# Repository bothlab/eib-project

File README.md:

# ST4 Intan Amplifier Boards & EIBs

Electrode Interface Boards and Amplifier Boards for use with the Intan RHD DAQ system

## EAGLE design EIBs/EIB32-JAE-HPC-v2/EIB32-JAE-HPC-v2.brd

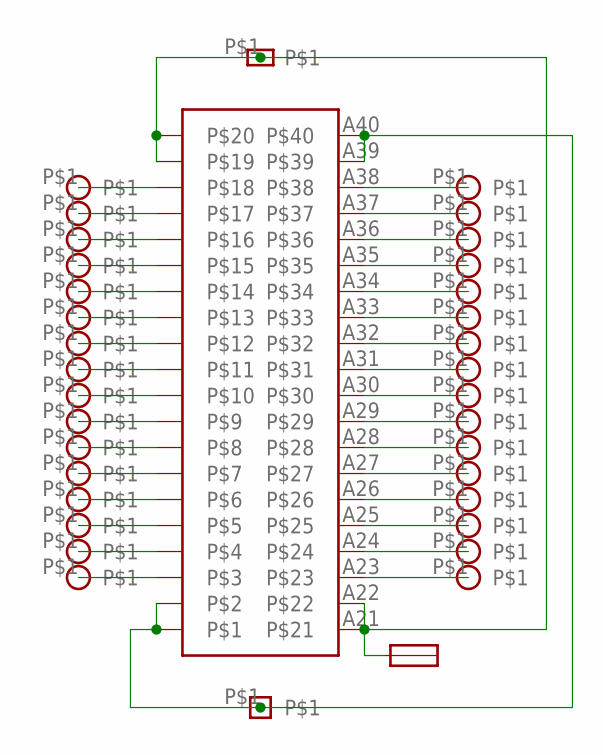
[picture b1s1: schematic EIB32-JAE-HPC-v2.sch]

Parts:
U$1: WR-40SB-VFH30
U$2: EIB-GND-HOLE-PAD-SMALL
U$3: EIB-GND-HOLE-PAD
U$4: JMP-PAD-SMALL
U$5, U$6, U$7, U$8, U$9, U$10, U$11, U$12, U$13, U$14, U$15, U$16, U$17, U$18, U$19, U$20, U$23, U$24, U$25, U$26, U$27, U$28, U$29, U$30, U$31, U$32, U$33, U$34, U$35, U$36, U$37, U$38: EIB-TETRODE-HOLE-RS-PAD

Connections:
unnamed: U$1.A19, U$1.A20, U$1.A21, U$1.A22, U$2.P$1, U$4.P$1
unnamed: U$1.A1, U$1.A2, U$1.A39, U$1.A40, U$3.P$1
unnamed: U$1.A18, U$5.P$1
unnamed: U$1.A17, U$6.P$1
unnamed: U$1.A16, U$7.P$1
unnamed: U$1.A15, U$8.P$1
unnamed: U$1.A14, U$9.P$1
unnamed: U$1.A13, U$10.P$1
unnamed: U$1.A12, U$11.P$1
unnamed: U$1.A11, U$12.P$1
unnamed: U$1.A10, U$13.P$1
unnamed: U$1.A9, U$14.P$1
unnamed: U$1.A8, U$15.P$1
unnamed: U$1.A7, U$16.P$1
unnamed: U$1.A6, U$17.P$1
unnamed: U$1.A5, U$18.P$1
unnamed: U$1.A4, U$19.P$1
unnamed: U$1.A3, U$20.P$1
unnamed: U$1.A38, U$23.P$1
unnamed: U$1.A37, U$24.P$1
unnamed: U$1.A36, U$25.P$1
unnamed: U$1.A35, U$26.P$1
unnamed: U$1.A34, U$27.P$1
unnamed: U$1.A33, U$28.P$1
unnamed: U$1.A32, U$29.P$1
unnamed: U$1.A31, U$30.P$1
unnamed: U$1.A30, U$31.P$1
unnamed: U$1.A29, U$32.P$1
unnamed: U$1.A28, U$33.P$1
unnamed: U$1.A27, U$34.P$1
unnamed: U$1.A26, U$35.P$1
unnamed: U$1.A25, U$36.P$1
unnamed: U$1.A24, U$37.P$1
unnamed: U$1.A23, U$38.P$1

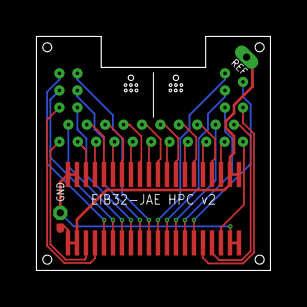
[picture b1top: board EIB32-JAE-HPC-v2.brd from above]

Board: 2 copper layers, 13.0 x 13.0 mm, 36 parts (0 on the bottom side), 34 nets.

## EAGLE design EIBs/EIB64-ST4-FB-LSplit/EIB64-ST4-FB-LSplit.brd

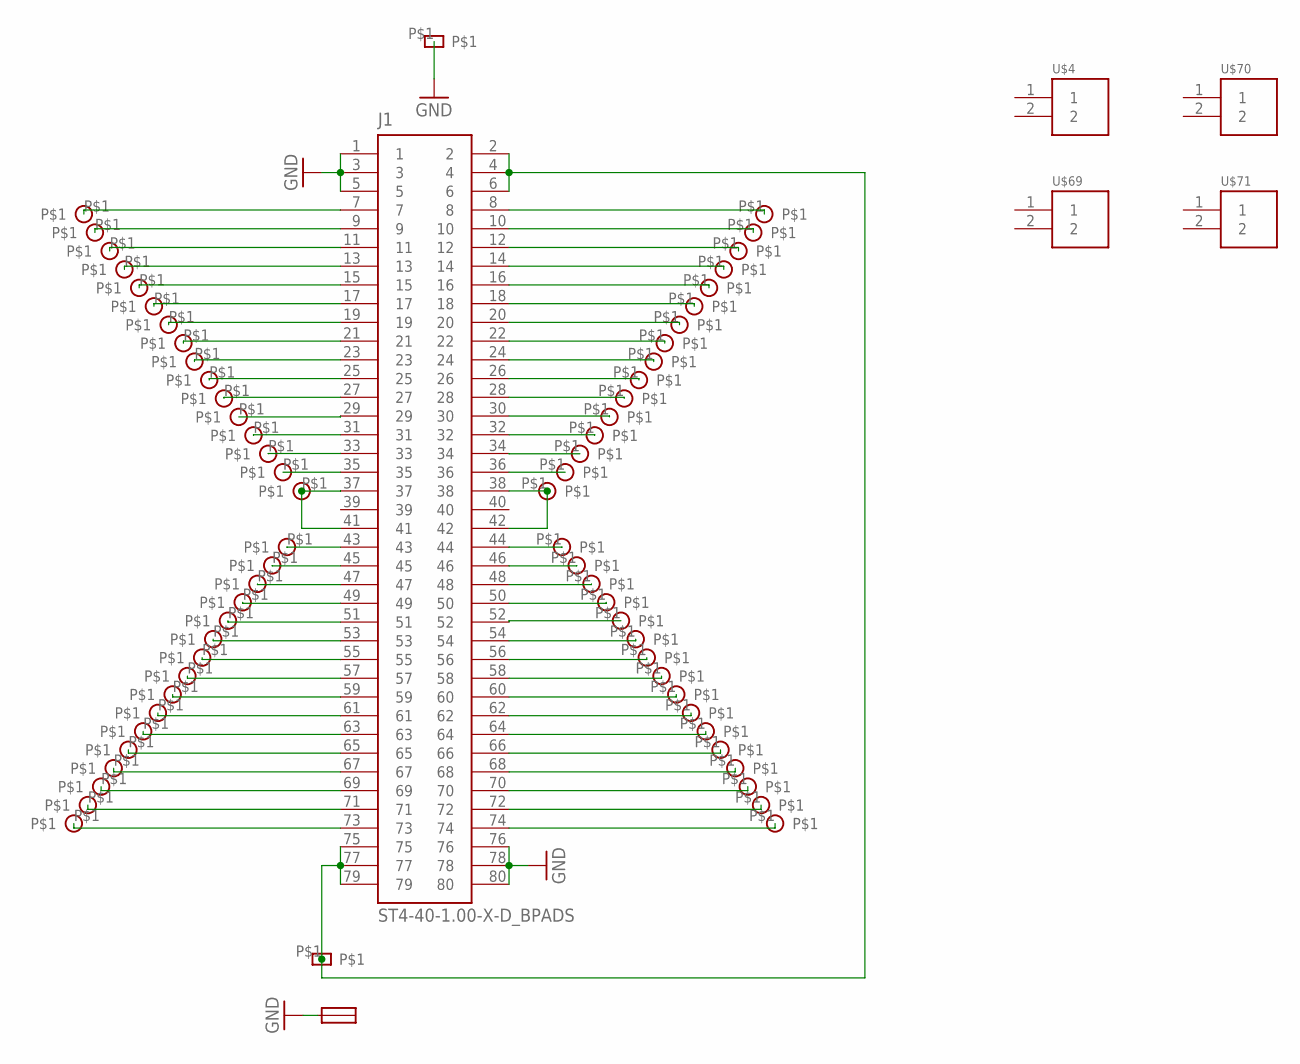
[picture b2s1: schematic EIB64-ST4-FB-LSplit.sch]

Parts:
J1: ST4-40-1.00-X-D_BPADS
U$1, U$3: EIB-GND-HOLE-PAD-SMALL
U$2: JMP-PAD-SMALL
U$4, U$69, U$70, U$71: THCONLY_TMS-102-XX-XX-S
U$5, U$6, U$7, U$8, U$9, U$10, U$11, U$12, U$13, U$14, U$15, U$16, U$17, U$18, U$19, U$20, U$21, U$22, U$23, U$24, U$25, U$26, U$27, U$28, U$29, U$30, U$31, U$32, U$33, U$34, U$35, U$36, U$37, U$38, U$39, U$40, U$41, U$42, U$43, U$44, U$45, U$46, U$47, U$48, U$49, U$50, U$51, U$52, U$53, U$54, U$55, U$56, U$57, U$58, U$59, U$60, U$61, U$62, U$63, U$64, U$65, U$66, U$67, U$68: EIB-TETRODE-HOLE-RS-PAD

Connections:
GND: J1.1, J1.3, J1.5, J1.76, J1.78, J1.80, U$1.P$1, U$2.P$1
unnamed: J1.2, J1.4, J1.6, J1.75, J1.77, J1.79, U$3.P$1
unnamed: J1.35, U$7.P$1
unnamed: J1.36, U$5.P$1
unnamed: J1.34, U$9.P$1
unnamed: J1.20, U$16.P$1
unnamed: J1.22, U$15.P$1
unnamed: J1.24, U$14.P$1
unnamed: J1.26, U$13.P$1
unnamed: J1.28, U$12.P$1
unnamed: J1.30, U$11.P$1
unnamed: J1.37, J1.41, U$8.P$1
unnamed: J1.32, U$10.P$1
unnamed: J1.74, U$52.P$1
unnamed: J1.18, U$17.P$1
unnamed: J1.16, U$18.P$1
unnamed: J1.14, U$19.P$1
unnamed: J1.12, U$20.P$1
unnamed: J1.10, U$21.P$1
unnamed: J1.8, U$22.P$1
unnamed: J1.33, U$23.P$1
unnamed: J1.31, U$24.P$1
unnamed: J1.29, U$25.P$1
unnamed: J1.27, U$26.P$1
unnamed: J1.25, U$27.P$1
unnamed: J1.23, U$28.P$1
unnamed: J1.21, U$29.P$1
unnamed: J1.19, U$30.P$1
unnamed: J1.17, U$31.P$1
unnamed: J1.15, U$32.P$1
unnamed: J1.13, U$33.P$1
unnamed: J1.11, U$34.P$1
unnamed: J1.9, U$35.P$1
unnamed: J1.7, U$36.P$1
unnamed: J1.72, U$51.P$1
unnamed: J1.70, U$50.P$1
unnamed: J1.68, U$49.P$1
unnamed: J1.66, U$48.P$1
unnamed: J1.64, U$47.P$1
unnamed: J1.62, U$46.P$1
unnamed: J1.60, U$45.P$1
unnamed: J1.58, U$44.P$1
unnamed: J1.56, U$43.P$1
unnamed: J1.54, U$42.P$1
unnamed: J1.52, U$41.P$1
unnamed: J1.50, U$40.P$1
unnamed: J1.48, U$39.P$1
unnamed: J1.46, U$38.P$1
unnamed: J1.44, U$37.P$1
unnamed: J1.38, J1.42, U$6.P$1
unnamed: J1.43, U$53.P$1
unnamed: J1.45, U$54.P$1
unnamed: J1.47, U$55.P$1
unnamed: J1.49, U$56.P$1
unnamed: J1.51, U$57.P$1
unnamed: J1.53, U$58.P$1
unnamed: J1.55, U$59.P$1
unnamed: J1.57, U$60.P$1
unnamed: J1.59, U$61.P$1
unnamed: J1.61, U$62.P$1
unnamed: J1.63, U$63.P$1
unnamed: J1.65, U$64.P$1
unnamed: J1.67, U$65.P$1
unnamed: J1.69, U$66.P$1
unnamed: J1.71, U$67.P$1
unnamed: J1.73, U$68.P$1

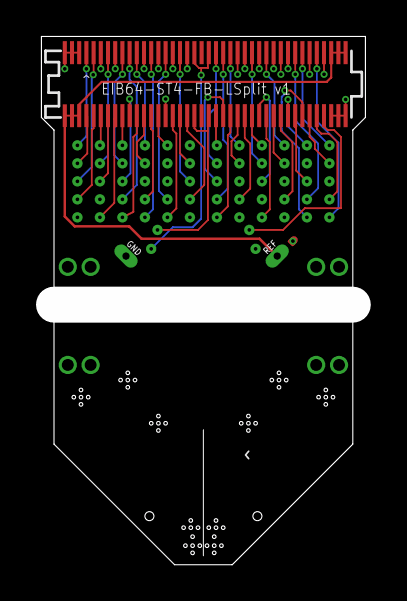
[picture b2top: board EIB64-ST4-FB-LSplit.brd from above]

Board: 4 copper layers, 18.0 x 29.4 mm, 72 parts (0 on the bottom side), 66 nets.

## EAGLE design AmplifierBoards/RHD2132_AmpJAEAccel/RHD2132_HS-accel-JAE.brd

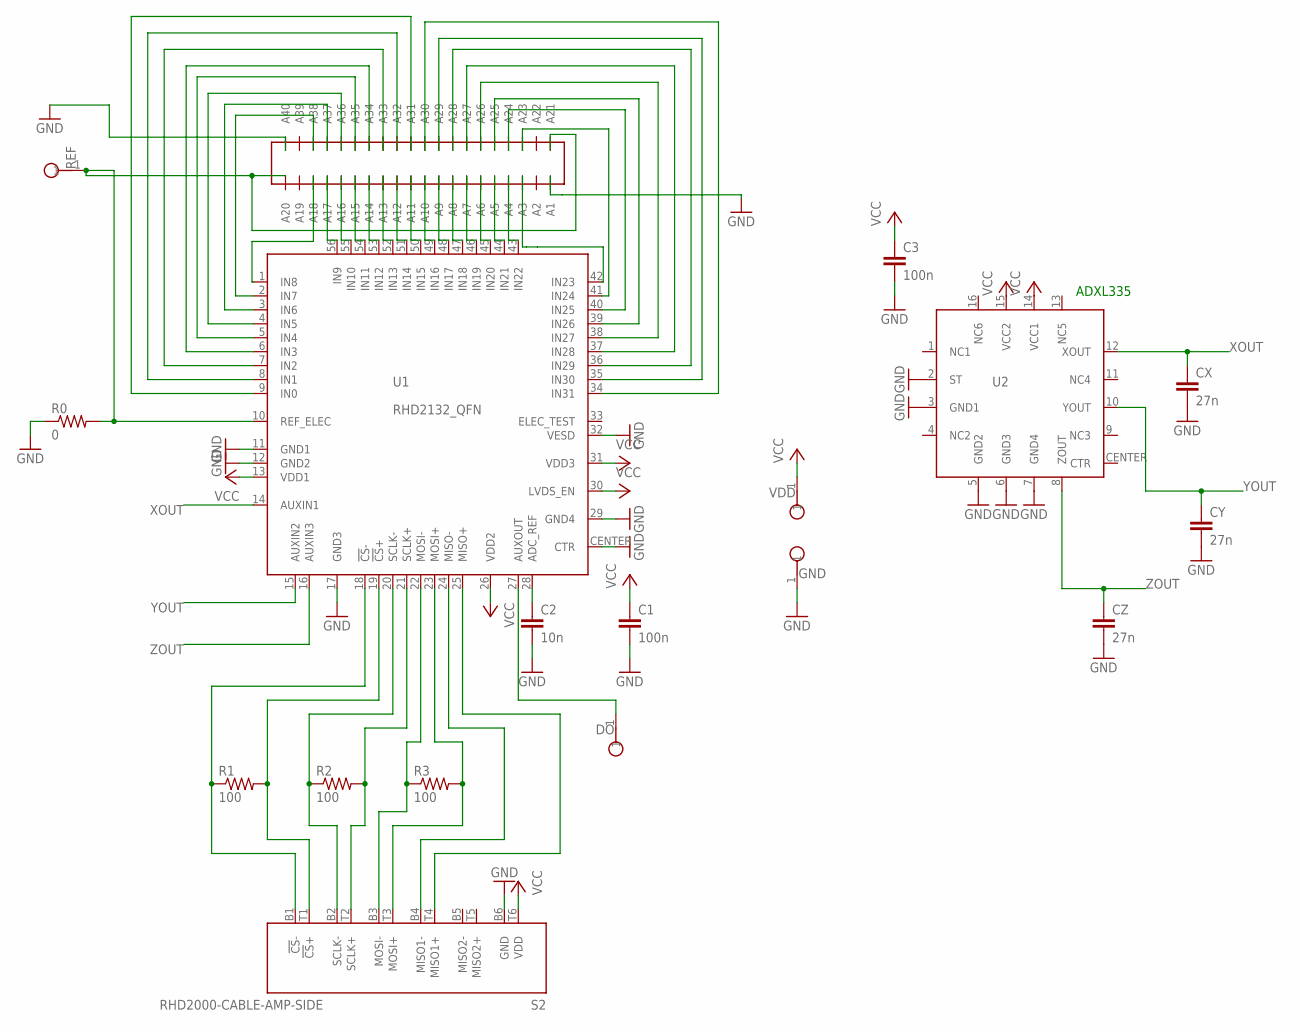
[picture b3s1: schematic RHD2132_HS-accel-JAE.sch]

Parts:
C1, C3: 100n; 0402
C2: 10n; 0402
CX: 27n; 0402
CY: 27n; 0402
CZ: 27n; 0402
DO: TESTPOINT_SMALL
GND: TESTPOINT_SMALL
R0: 0; 0402
R1, R2, R3: 100; 0402
REF: TESTPOINT_SMALL
S2: RHD2000-CABLE-AMP-SIDE; OMNETICS_PZN-12-AA
U1: RHD2132_QFN; QFN56_8_X_8_LARGE
U2: ADXL335
U$1: WR-40P-HFHD
VDD: TESTPOINT_SMALL

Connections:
GND: C1.2, C2.2, C3.2, CX.2, CY.2, CZ.2, GND.1, R0.1, S2.B6 (GND), U1.11 (GND1), U1.12 (GND2), U1.17 (GND3), U1.29 (GND4), U1.32 (VESD), U1.CENTER (CTR), U2.2 (ST), U2.3 (GND1), U2.5 (GND2), U2.6 (GND3), U2.7 (GND4), U$1.P$1 (A1), U$1.P$40 (A40)
unnamed: U1.3 (IN6), U$1.P$37 (A37)
unnamed: U1.2 (IN7), U$1.P$38 (A38)
unnamed: U1.4 (IN5), U$1.P$36 (A36)
unnamed: U1.5 (IN4), U$1.P$35 (A35)
unnamed: U1.6 (IN3), U$1.P$34 (A34)
unnamed: U1.7 (IN2), U$1.P$33 (A33)
unnamed: U1.8 (IN1), U$1.P$32 (A32)
unnamed: U1.9 (IN0), U$1.P$31 (A31)
unnamed: U1.34 (IN31), U$1.P$30 (A30)
unnamed: R1.1, S2.B1 (!CS!-), U1.18 (!CS!-)
unnamed: U1.41 (IN24), U$1.P$23 (A23)
unnamed: U1.40 (IN25), U$1.P$24 (A24)
unnamed: U1.39 (IN26), U$1.P$25 (A25)
unnamed: U1.38 (IN27), U$1.P$26 (A26)
unnamed: U1.37 (IN28), U$1.P$27 (A27)
unnamed: U1.36 (IN29), U$1.P$28 (A28)
unnamed: U1.35 (IN30), U$1.P$29 (A29)
unnamed: U1.56 (IN9), U$1.P$17 (A17)
unnamed: U1.55 (IN10), U$1.P$16 (A16)
unnamed: U1.54 (IN11), U$1.P$15 (A15)
unnamed: U1.53 (IN12), U$1.P$14 (A14)
unnamed: U1.52 (IN13), U$1.P$13 (A13)
unnamed: U1.51 (IN14), U$1.P$12 (A12)
unnamed: U1.50 (IN15), U$1.P$11 (A11)
unnamed: U1.49 (IN16), U$1.P$10 (A10)
unnamed: U1.48 (IN17), U$1.P$9 (A9)
unnamed: U1.47 (IN18), U$1.P$8 (A8)
unnamed: U1.46 (IN19), U$1.P$7 (A7)
unnamed: U1.45 (IN20), U$1.P$6 (A6)
unnamed: U1.44 (IN21), U$1.P$5 (A5)
unnamed: U1.43 (IN22), U$1.P$4 (A4)
unnamed: U1.1 (IN8), U$1.P$18 (A18)
unnamed: U1.42 (IN23), U$1.P$3 (A3)
unnamed: R1.2, S2.T1 (!CS!+), U1.19 (!CS!+)
unnamed: R2.1, S2.B2 (SCLK-), U1.20 (SCLK-)
unnamed: R2.2, S2.T2 (SCLK+), U1.21 (SCLK+)
unnamed: R3.1, S2.B3 (MOSI-), U1.22 (MOSI-)
unnamed: R3.2, S2.T3 (MOSI+), U1.23 (MOSI+)
unnamed: S2.B4 (MISO1-), U1.24 (MISO-)
unnamed: S2.T4 (MISO1+), U1.25 (MISO+)
unnamed: C2.1, U1.28 (ADC_REF)
unnamed: DO.1, U1.27 (AUXOUT)
unnamed: R0.2, REF.1, U1.10 (REF_ELEC), U$1.P$20 (A20)
VCC: C1.1, C3.1, S2.T6 (VDD), U1.13 (VDD1), U1.26 (VDD2), U1.30 (LVDS_EN), U1.31 (VDD3), U2.14 (VCC1), U2.15 (VCC2), VDD.1
XOUT: CX.1, U1.14 (AUXIN1), U2.12 (XOUT)
YOUT: CY.1, U1.15 (AUXIN2), U2.10 (YOUT)
ZOUT: CZ.1, U1.16 (AUXIN3), U2.8 (ZOUT)

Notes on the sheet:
ADXL335

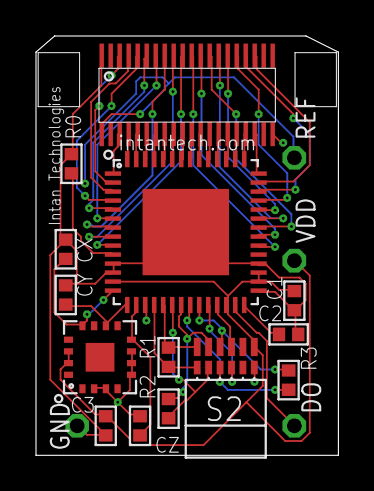
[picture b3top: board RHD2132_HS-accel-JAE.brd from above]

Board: 4 copper layers, 16.8 x 23.3 mm, 18 parts (0 on the bottom side), 48 nets.

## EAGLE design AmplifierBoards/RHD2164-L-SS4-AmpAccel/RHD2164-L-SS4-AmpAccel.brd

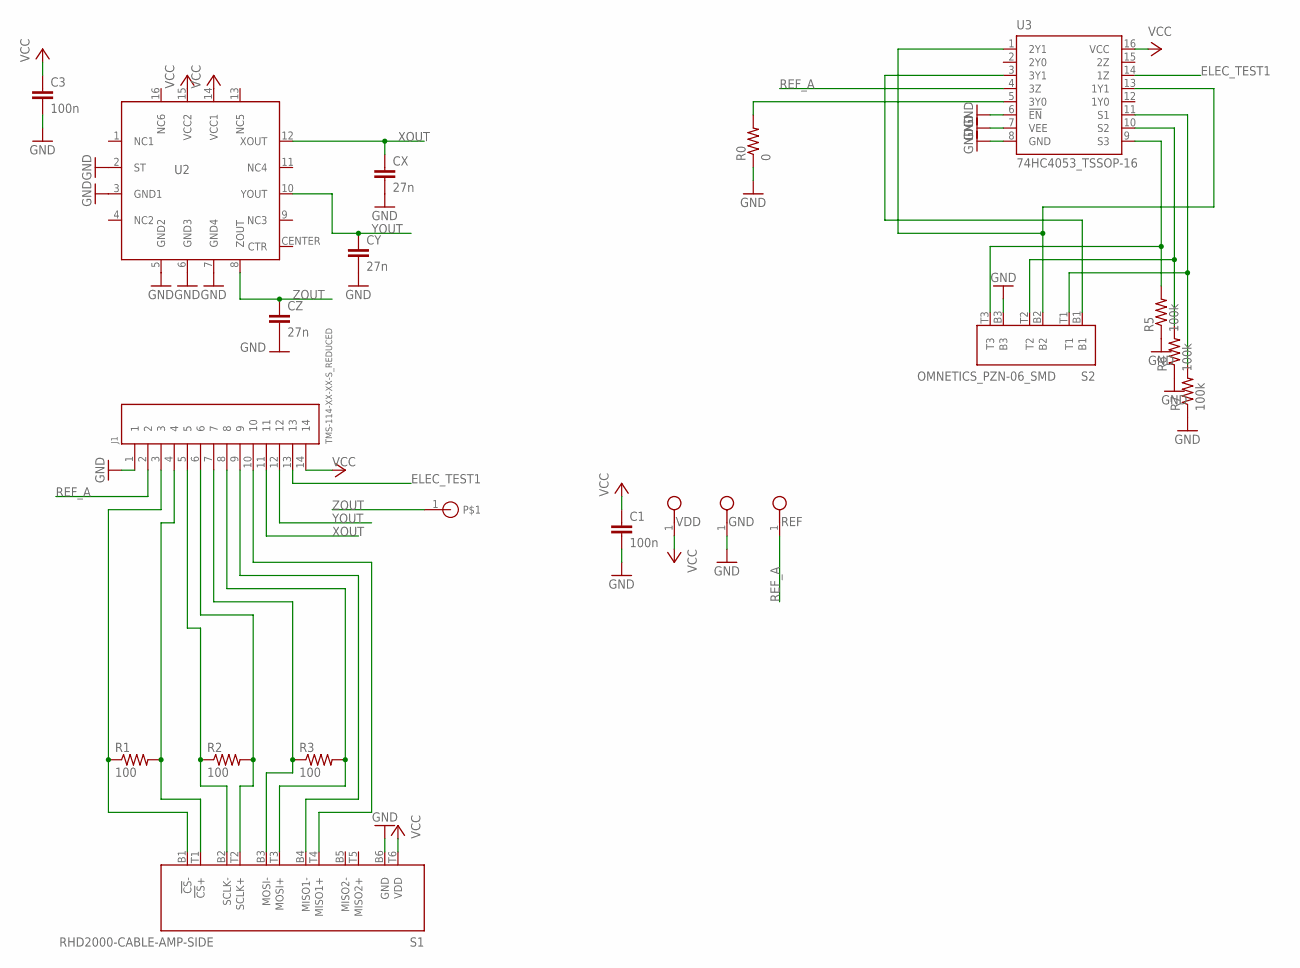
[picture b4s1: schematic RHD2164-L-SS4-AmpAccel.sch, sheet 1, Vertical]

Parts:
C1, C3: 100n; 0402
CX: 27n; 0402
CY: 27n; 0402
CZ: 27n; 0402
GND: TESTPOINT_SMALL
J1: TMS-114-XX-XX-S_REDUCED
R0: 0; 0402
R1, R2, R3: 100; 0201
R5, R6, R7: 100k; 0201
REF: TESTPOINT_SMALL
S1: RHD2000-CABLE-AMP-SIDE; OMNETICS_PZN-12-AA
S2: OMNETICS_PZN-06_SMD; OMNETICS_PZN-06-AA
U2: ADXL335_IDAX
U3: 74HC4053_TSSOP-16; TSSOP-16
U$1: PIN_HOLE
VDD: TESTPOINT_SMALL

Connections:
CS-: J1.3, R1.1, S1.B1 (!CS!-)
ELEC_TEST1: J1.13, U3.14 (1Z)
GND: C1.2, C3.2, CX.2, CY.2, CZ.2, GND.1, J1.1, R0.1, R5.1, R6.1, R7.1, S1.B6 (GND), S2.B3, U2.2 (ST), U2.3 (GND1), U2.5 (GND2), U2.6 (GND3), U2.7 (GND4), U3.6 (!EN!), U3.7 (VEE), U3.8 (GND)
unnamed: R0.2, U3.5 (3Y0)
unnamed: J1.4, R1.2, S1.T1 (!CS!+)
unnamed: J1.5, R2.1, S1.B2 (SCLK-)
unnamed: J1.6, R2.2, S1.T2 (SCLK+)
unnamed: J1.7, R3.1, S1.B3 (MOSI-)
unnamed: J1.8, R3.2, S1.T3 (MOSI+)
unnamed: J1.9, S1.B4 (MISO1-)
unnamed: J1.10, S1.T4 (MISO1+)
unnamed: R7.2, S2.T1, U3.11 (S1)
unnamed: R6.2, S2.T2, U3.10 (S2)
unnamed: R5.2, S2.T3, U3.9 (S3)
unnamed: S2.B1, U3.3 (3Y1)
unnamed: S2.B2, U3.1 (2Y1), U3.13 (1Y1)
REF_A: J1.2, REF.1, U3.4 (3Z)
VCC: C1.1, C3.1, J1.14, S1.T6 (VDD), U2.14 (VCC1), U2.15 (VCC2), U3.16 (VCC), VDD.1
XOUT: CX.1, J1.11, U2.12 (XOUT)
YOUT: CY.1, J1.12, U2.10 (YOUT)
ZOUT: CZ.1, U2.8 (ZOUT), U$1.1

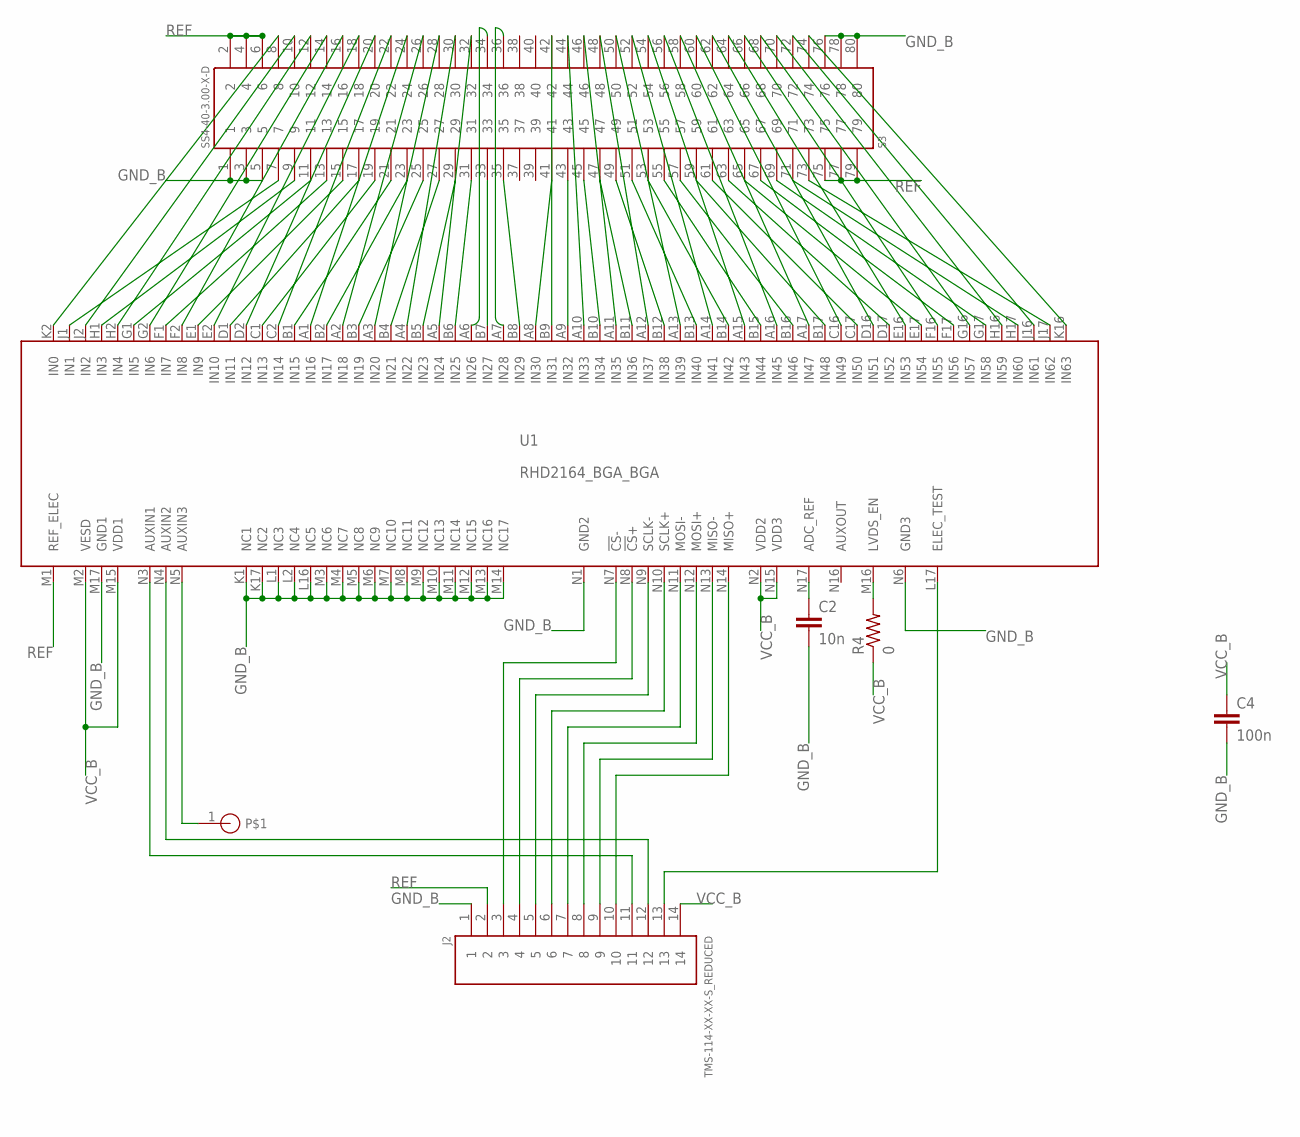
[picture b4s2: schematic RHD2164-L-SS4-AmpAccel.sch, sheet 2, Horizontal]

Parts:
C2: 10n; 0201
C4: 100n; 0402
J2: TMS-114-XX-XX-S_REDUCED
R4: 0; 0402
S3: SS4-40-3.00-X-D
U1: RHD2164_BGA_BGA; BGA104_9X7
U$2: PIN_HOLE

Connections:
GND_B: C2.2, C4.2, J2.1, S3.1, S3.3, S3.5, S3.76, S3.78, S3.80, U1.K1 (NC1), U1.K17 (NC2), U1.L1 (NC3), U1.L2 (NC4), U1.L16 (NC5), U1.M3 (NC6), U1.M4 (NC7), U1.M5 (NC8), U1.M6 (NC9), U1.M7 (NC10), U1.M8 (NC11), U1.M9 (NC12), U1.M10 (NC13), U1.M11 (NC14), U1.M12 (NC15), U1.M13 (NC16), U1.M14 (NC17), U1.M17 (GND1), U1.N1 (GND2), U1.N6 (GND3)
unnamed: C2.1, U1.N17 (ADC_REF)
unnamed: S3.8, U1.K2 (IN0)
unnamed: S3.7, U1.J1 (IN1)
unnamed: S3.10, U1.J2 (IN2)
unnamed: S3.9, U1.H1 (IN3)
unnamed: S3.12, U1.H2 (IN4)
unnamed: S3.11, U1.G1 (IN5)
unnamed: S3.14, U1.G2 (IN6)
unnamed: S3.13, U1.F1 (IN7)
unnamed: J2.4, U1.N8 (!CS!+)
unnamed: J2.6, U1.N10 (SCLK+)
unnamed: J2.8, U1.N12 (MOSI+)
unnamed: J2.9, U1.N13 (MISO-)
unnamed: J2.10, U1.N14 (MISO+)
unnamed: S3.16, U1.F2 (IN8)
unnamed: S3.15, U1.E1 (IN9)
unnamed: S3.18, U1.E2 (IN10)
unnamed: S3.17, U1.D1 (IN11)
unnamed: S3.20, U1.D2 (IN12)
unnamed: S3.19, U1.C1 (IN13)
unnamed: S3.22, U1.C2 (IN14)
unnamed: S3.21, U1.B1 (IN15)
unnamed: S3.24, U1.A1 (IN16)
unnamed: S3.23, U1.B2 (IN17)
unnamed: S3.26, U1.A2 (IN18)
unnamed: S3.25, U1.B3 (IN19)
unnamed: S3.74, U1.K16 (IN63)
unnamed: S3.73, U1.J17 (IN62)
unnamed: S3.72, U1.J16 (IN61)
unnamed: S3.71, U1.H17 (IN60)
unnamed: S3.70, U1.H16 (IN59)
unnamed: S3.69, U1.G17 (IN58)
unnamed: R4.2, U1.M16 (LVDS_EN)
unnamed: S3.68, U1.G16 (IN57)
unnamed: S3.67, U1.F17 (IN56)
unnamed: S3.66, U1.F16 (IN55)
unnamed: S3.65, U1.E17 (IN54)
unnamed: S3.64, U1.E16 (IN53)
unnamed: S3.63, U1.D17 (IN52)
unnamed: S3.62, U1.D16 (IN51)
unnamed: S3.61, U1.C17 (IN50)
unnamed: S3.60, U1.C16 (IN49)
unnamed: S3.59, U1.B17 (IN48)
unnamed: S3.58, U1.A17 (IN47)
unnamed: S3.57, U1.B16 (IN46)
unnamed: S3.56, U1.A16 (IN45)
unnamed: S3.55, U1.B15 (IN44)
unnamed: S3.54, U1.A15 (IN43)
unnamed: S3.53, U1.B14 (IN42)
unnamed: S3.52, U1.A14 (IN41)
unnamed: S3.51, U1.B13 (IN40)
unnamed: S3.28, U1.A3 (IN20)
unnamed: S3.27, U1.B4 (IN21)
unnamed: S3.30, U1.A4 (IN22)
unnamed: S3.29, U1.B5 (IN23)
unnamed: S3.32, U1.A5 (IN24)
unnamed: S3.31, U1.B6 (IN25)
unnamed: S3.34, U1.A6 (IN26)
unnamed: S3.33, U1.B7 (IN27)
unnamed: S3.50, U1.A13 (IN39)
unnamed: S3.49, U1.B12 (IN38)
unnamed: S3.48, U1.A12 (IN37)
unnamed: S3.47, U1.B11 (IN36)
unnamed: S3.46, U1.A11 (IN35)
unnamed: S3.45, U1.B10 (IN34)
unnamed: S3.44, U1.A10 (IN33)
unnamed: S3.43, U1.A9 (IN32)
unnamed: S3.42, U1.B9 (IN31)
unnamed: S3.41, U1.A8 (IN30)
unnamed: S3.36, U1.A7 (IN28)
unnamed: S3.35, U1.B8 (IN29)
unnamed: J2.13, U1.L17 (ELEC_TEST)
unnamed: J2.11, U1.N3 (AUXIN1)
unnamed: J2.12, U1.N4 (AUXIN2)
unnamed: U1.N5 (AUXIN3), U$2.1
unnamed: J2.3, U1.N7 (!CS!-)
unnamed: J2.5, U1.N9 (SCLK-)
unnamed: J2.7, U1.N11 (MOSI-)
REF: J2.2, S3.2, S3.4, S3.6, S3.75, S3.77, S3.79, U1.M1 (REF_ELEC)
VCC_B: C4.1, J2.14, R4.1, U1.M2 (VESD), U1.M15 (VDD1), U1.N2 (VDD2), U1.N15 (VDD3)

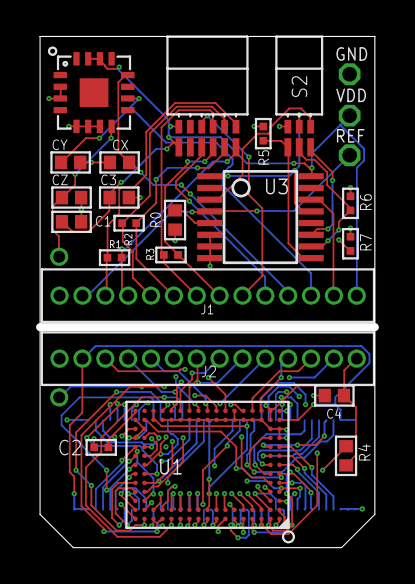
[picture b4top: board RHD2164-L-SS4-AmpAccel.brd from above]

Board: 4 copper layers, 18.6 x 28.4 mm, 28 parts (1 on the bottom side), 102 nets.

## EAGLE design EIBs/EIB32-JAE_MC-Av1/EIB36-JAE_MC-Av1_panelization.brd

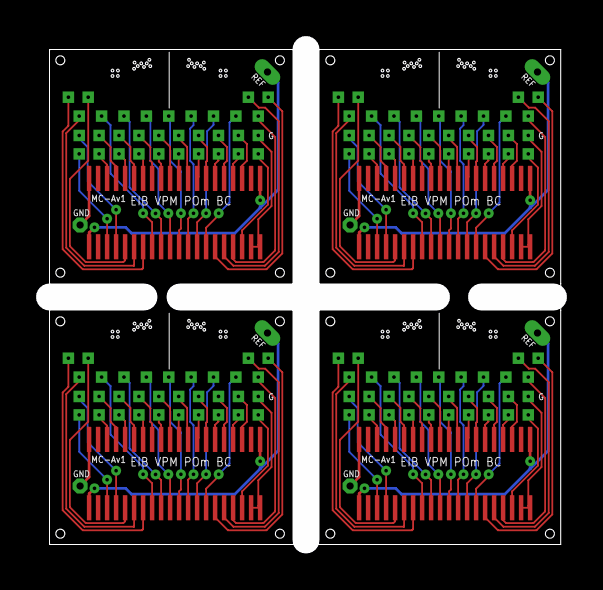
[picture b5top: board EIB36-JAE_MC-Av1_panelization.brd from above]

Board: 2 copper layers, 28.4 x 27.5 mm, 144 parts (0 on the bottom side), 140 nets.

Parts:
U$1, U$4, U$73, U$109: WR-40SB-VFH30
U$2, U$71, U$107, U$143: EIB-GND-HOLE-PAD-SMALL
U$3, U$72, U$108, U$144: EIB-GND-HOLE-PAD
U$5, U$6, U$7, U$8, U$9, U$10, U$11, U$12, U$13, U$14, U$15, U$16, U$17, U$18, U$19, U$20, U$21, U$22, U$23, U$24, U$25, U$26, U$27, U$28, U$29, U$30, U$31, U$32, U$33, U$34, U$35, U$36, U$37, U$38, U$39, U$40, U$41, U$42, U$43, U$44, U$45, U$46, U$47, U$48, U$49, U$50, U$51, U$52, U$53, U$54, U$55, U$56, U$57, U$58, U$59, U$60, U$61, U$62, U$63, U$64, U$65, U$66, U$67, U$68, U$69, U$70, U$74, U$75, U$76, U$77, U$78, U$79, U$80, U$81, U$82, U$83, U$84, U$85, U$86, U$87, U$88, U$89, U$90, U$91, U$92, U$93, U$94, U$95, U$96, U$97, U$98, U$99, U$100, U$101, U$102, U$103, U$104, U$105, U$106, U$110, U$111, U$112, U$113, U$114, U$115, U$116, U$117, U$118, U$119, U$120, U$121, U$122, U$123, U$124, U$125, U$126, U$127, U$128, U$129, U$130, U$131, U$132, U$133, U$134, U$135, U$136, U$137, U$138, U$139, U$140, U$141, U$142: EIB-TETRODE-HOLE-PAD

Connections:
unnamed: U$1.A20, U$1.A21, U$2.P$1
unnamed: U$1.A1, U$3.P$1
unnamed: U$4.A20, U$4.A21, U$71.P$1
unnamed: U$4.A18, U$21.P$1
unnamed: U$4.A17, U$39.P$1
unnamed: U$1.A18, U$5.P$1
unnamed: U$1.A17, U$6.P$1
unnamed: U$1.A16, U$7.P$1
unnamed: U$1.A15, U$8.P$1
unnamed: U$1.A14, U$9.P$1
unnamed: U$1.A13, U$10.P$1
unnamed: U$1.A12, U$11.P$1
unnamed: U$1.A11, U$12.P$1
unnamed: U$1.A10, U$13.P$1
unnamed: U$1.A9, U$14.P$1
unnamed: U$1.A8, U$15.P$1
unnamed: U$1.A7, U$16.P$1
unnamed: U$1.A6, U$17.P$1
unnamed: U$1.A5, U$18.P$1
unnamed: U$1.A4, U$19.P$1
unnamed: U$1.A3, U$20.P$1
unnamed: U$4.A16, U$40.P$1
unnamed: U$1.A39, U$1.A40, U$22.P$1
unnamed: U$1.A38, U$23.P$1
unnamed: U$1.A37, U$24.P$1
unnamed: U$1.A36, U$25.P$1
unnamed: U$1.A35, U$26.P$1
unnamed: U$1.A34, U$27.P$1
unnamed: U$1.A33, U$28.P$1
unnamed: U$1.A32, U$29.P$1
unnamed: U$1.A31, U$30.P$1
unnamed: U$1.A30, U$31.P$1
unnamed: U$1.A29, U$32.P$1
unnamed: U$1.A28, U$33.P$1
unnamed: U$1.A27, U$34.P$1
unnamed: U$1.A26, U$35.P$1
unnamed: U$1.A25, U$36.P$1
unnamed: U$1.A24, U$37.P$1
unnamed: U$1.A23, U$38.P$1
unnamed: U$4.A15, U$41.P$1
unnamed: U$4.A14, U$42.P$1
unnamed: U$4.A13, U$43.P$1
unnamed: U$4.A12, U$44.P$1
unnamed: U$4.A11, U$45.P$1
unnamed: U$4.A10, U$46.P$1
unnamed: U$4.A9, U$47.P$1
unnamed: U$4.A8, U$48.P$1
unnamed: U$4.A7, U$49.P$1
unnamed: U$4.A6, U$50.P$1
unnamed: U$4.A5, U$51.P$1
unnamed: U$4.A4, U$52.P$1
unnamed: U$4.A3, U$53.P$1
unnamed: U$4.A39, U$4.A40, U$54.P$1
unnamed: U$4.A38, U$55.P$1
unnamed: U$4.A37, U$56.P$1
unnamed: U$4.A36, U$57.P$1
unnamed: U$4.A35, U$58.P$1
unnamed: U$4.A34, U$59.P$1
unnamed: U$4.A33, U$60.P$1
unnamed: U$4.A32, U$61.P$1
unnamed: U$4.A31, U$62.P$1
unnamed: U$4.A30, U$63.P$1
unnamed: U$4.A29, U$64.P$1
unnamed: U$4.A28, U$65.P$1
unnamed: U$4.A27, U$66.P$1
unnamed: U$4.A26, U$67.P$1
unnamed: U$4.A25, U$68.P$1
unnamed: U$4.A24, U$69.P$1
unnamed: U$4.A23, U$70.P$1
unnamed: U$4.A1, U$72.P$1
unnamed: U$73.A20, U$73.A21, U$107.P$1
unnamed: U$73.A18, U$74.P$1
unnamed: U$73.A17, U$75.P$1
unnamed: U$73.A16, U$76.P$1
unnamed: U$73.A15, U$77.P$1
unnamed: U$73.A14, U$78.P$1
unnamed: U$73.A13, U$79.P$1
unnamed: U$73.A12, U$80.P$1
unnamed: U$73.A11, U$81.P$1
unnamed: U$73.A10, U$82.P$1
unnamed: U$73.A9, U$83.P$1
unnamed: U$73.A8, U$84.P$1
unnamed: U$73.A7, U$85.P$1
unnamed: U$73.A6, U$86.P$1
unnamed: U$73.A5, U$87.P$1
unnamed: U$73.A4, U$88.P$1
unnamed: U$73.A3, U$89.P$1
unnamed: U$73.A39, U$73.A40, U$90.P$1
unnamed: U$73.A38, U$91.P$1
unnamed: U$73.A37, U$92.P$1
unnamed: U$73.A36, U$93.P$1
unnamed: U$73.A35, U$94.P$1
unnamed: U$73.A34, U$95.P$1
unnamed: U$73.A33, U$96.P$1
unnamed: U$73.A32, U$97.P$1
unnamed: U$73.A31, U$98.P$1
unnamed: U$73.A30, U$99.P$1
unnamed: U$73.A29, U$100.P$1
unnamed: U$73.A28, U$101.P$1
unnamed: U$73.A27, U$102.P$1
unnamed: U$73.A26, U$103.P$1
unnamed: U$73.A25, U$104.P$1
unnamed: U$73.A24, U$105.P$1
unnamed: U$73.A23, U$106.P$1
unnamed: U$73.A1, U$108.P$1
unnamed: U$109.A20, U$109.A21, U$143.P$1
unnamed: U$109.A18, U$110.P$1
unnamed: U$109.A17, U$111.P$1
unnamed: U$109.A16, U$112.P$1
unnamed: U$109.A15, U$113.P$1
unnamed: U$109.A14, U$114.P$1
unnamed: U$109.A13, U$115.P$1
unnamed: U$109.A12, U$116.P$1
unnamed: U$109.A11, U$117.P$1
unnamed: U$109.A10, U$118.P$1
unnamed: U$109.A9, U$119.P$1
unnamed: U$109.A8, U$120.P$1
unnamed: U$109.A7, U$121.P$1
unnamed: U$109.A6, U$122.P$1
unnamed: U$109.A5, U$123.P$1
unnamed: U$109.A4, U$124.P$1
unnamed: U$109.A3, U$125.P$1
unnamed: U$109.A39, U$109.A40, U$126.P$1
unnamed: U$109.A38, U$127.P$1
unnamed: U$109.A37, U$128.P$1
unnamed: U$109.A36, U$129.P$1
unnamed: U$109.A35, U$130.P$1
unnamed: U$109.A34, U$131.P$1
unnamed: U$109.A33, U$132.P$1
unnamed: U$109.A32, U$133.P$1
unnamed: U$109.A31, U$134.P$1
unnamed: U$109.A30, U$135.P$1
unnamed: U$109.A29, U$136.P$1
unnamed: U$109.A28, U$137.P$1
unnamed: U$109.A27, U$138.P$1
unnamed: U$109.A26, U$139.P$1
unnamed: U$109.A25, U$140.P$1
unnamed: U$109.A24, U$141.P$1
unnamed: U$109.A23, U$142.P$1
unnamed: U$109.A1, U$144.P$1

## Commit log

2020-09-11 Update license
2020-09-11 Add gitignore
2020-09-11 Add (most) existing project files
